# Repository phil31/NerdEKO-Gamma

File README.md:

# Nerd-EKO-Gamma Miner

fork of the NerdOCTAXE-Gamma design (https://github.com/Patsch91/NerdOCTAXE-Gamma), with 12 x BM1370 (14TH/s SHA256)

- 6 layers PCB - Outer / Inner Copper Weight: 2 oz

Design fully tested and validated
consume about 230 Watts on 12V for about 14TH/s (Vcore 1100mV, Icore 180A)
use a 12V 40A PSU

be aware, need some knowledge and tools to build this board !
particulary attention : NEVER power up the board with the Vcore enable without proper heatsink (this will immediatly kill the ASICs !)

## License 
This hardware design is licensed under the TAPR Open Hardware License – Non-Commercial (OHL-NC).  
You are free to use, modify, and distribute for **non-commercial purposes**.  

**Commercial use requires explicit written permission from the copyright holder.**  
See the [LICENSE](LICENSE) file for details.

## Inspired by 
[Bitaxe](https://github.com/skot/bitaxe) 
[NerdAxe](https://github.com/BitMaker-hub)
[NerdOCTAXE](https://github.com/Patsch91/NerdOCTAXE-Gamma) 
[ESP-Miner-NerdQAxePlus](https://github.com/shufps/ESP-Miner-NerdQAxePlus)
[OSMU](https://osmu.wiki/)

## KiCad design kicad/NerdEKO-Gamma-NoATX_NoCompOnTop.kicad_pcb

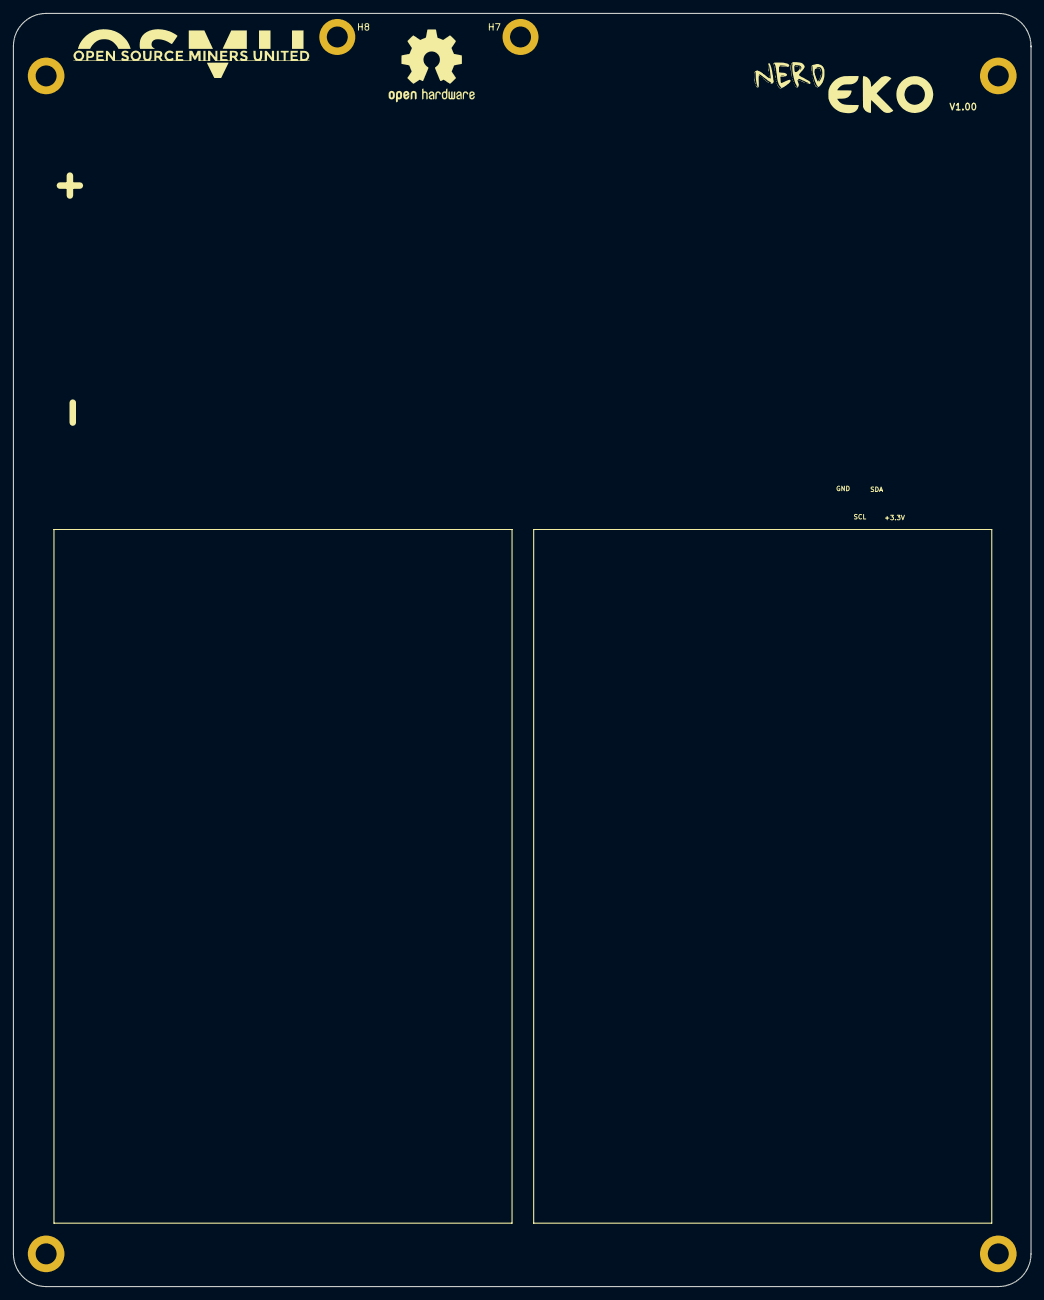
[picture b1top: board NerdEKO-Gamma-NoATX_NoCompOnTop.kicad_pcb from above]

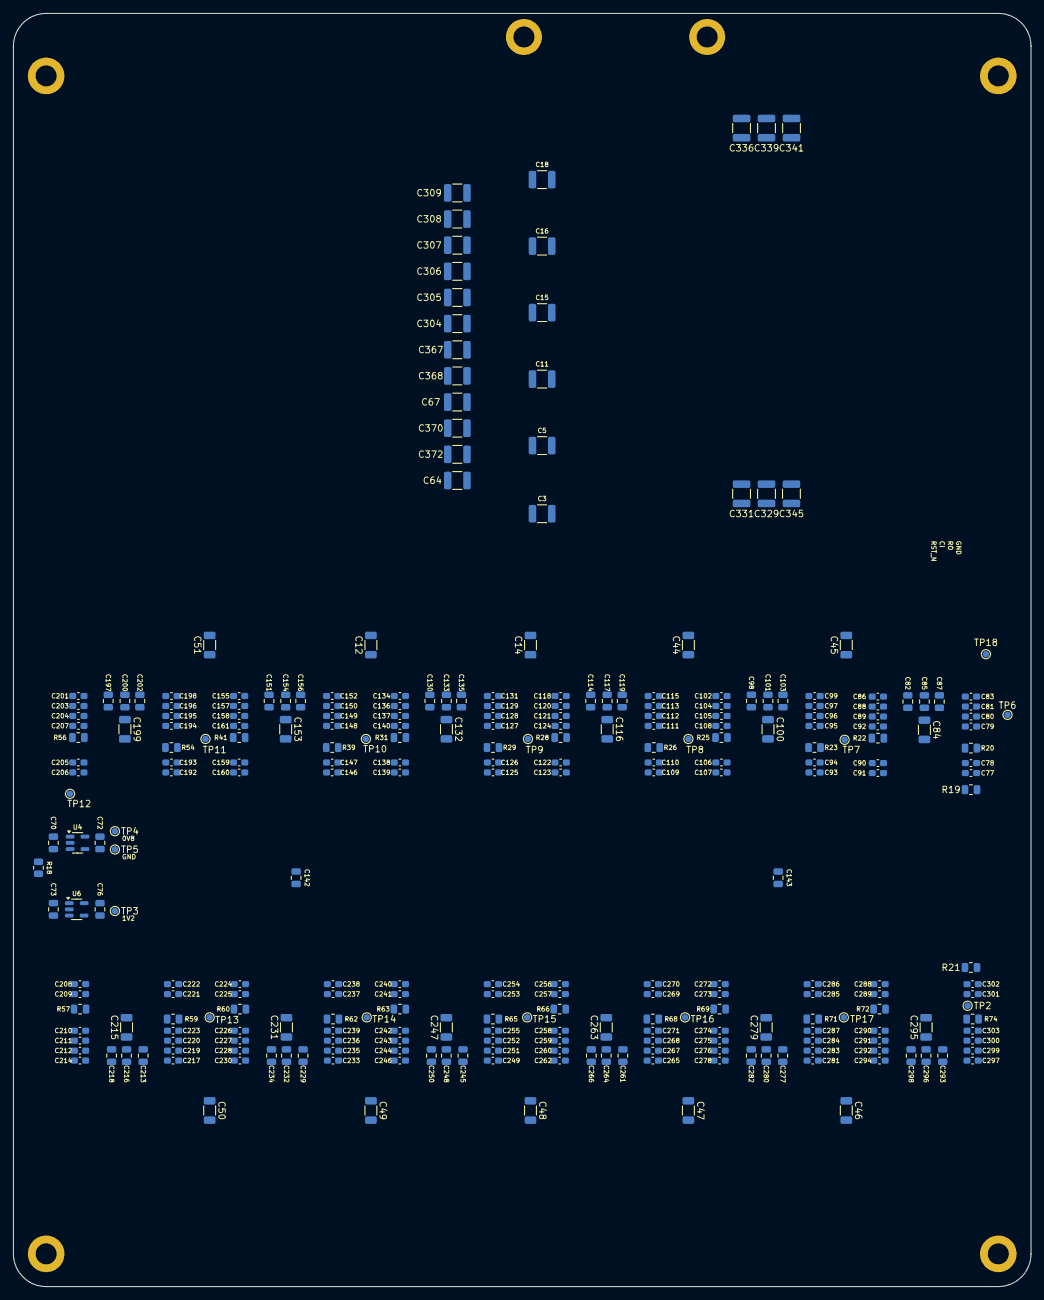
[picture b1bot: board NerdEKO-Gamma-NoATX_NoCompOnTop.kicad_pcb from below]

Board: 6 copper layers, 155.5 x 194.6 mm, 280 parts (278 on the bottom side), 79 nets.

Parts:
C3, C5, C11, C15, C16, C18, C64, C67, C304, C305, C306, C307, C308, C309, C367, C368, C370, C372: 330µF/4V; C_1210_3225Metric
C12, C14, C44, C45, C46, C47, C48, C49, C50, C51, C84, C100, C116, C132, C153, C199, C215, C231, C247, C263, C279, C295: 100µ/6.3V; C_1206_3216Metric
C70, C73, C87, C103, C119, C135, C142, C143, C156, C202, C218, C234, C250, C266, C282, C298: 100nF; C_0805_2012Metric
C72, C76, C85, C101, C117, C133, C154, C200, C216, C232, C248, C264, C280, C296: 1µF/25V; C_0805_2012Metric
C77, C78, C79, C80, C81, C83, C86, C88, C89, C90, C91, C92, C93, C94, C95, C96, C97, C99, C102, C104, C105, C106, C107, C108, C109, C110, C111, C112, C113, C115, C118, C120, C121, C122, C123, C124, C125, C126, C127, C128, C129, C131, C134, C136, C137, C138, C139, C140, C146, C147, C148, C149, C150, C152, C155, C157, C158, C159, C160, C161, C192, C193, C194, C195, C196, C198, C201, C203, C204, C205, C206, C207, C208, C209, C210, C211, C212, C214, C217, C219, C220, C221, C222, C223, C224, C225, C226, C227, C228, C230, C233, C235, C236, C237, C238, C239, C240, C241, C242, C243, C244, C246, C249, C251, C252, C253, C254, C255, C256, C257, C258, C259, C260, C262, C265, C267, C268, C269, C270, C271, C272, C273, C274, C275, C276, C278, C281, C283, C284, C285, C286, C287, C288, C289, C290, C291, C292, C294, C297, C299, C300, C301, C302, C303: 1µF/6.3V; C_0603_1608Metric_Pad1.08x0.95mm_HandSolder
C82, C98, C114, C130, C151, C197, C213, C229, C245, C261, C277, C293: 10µF/25V; C_0805_2012Metric
C329, C331, C336, C339, C341, C345: 22µ/25V; C_1210_3225Metric
H7, H8: MountingHole; MountingHole_3.2mm_M3_ISO14580_Pad
R18, R19, R21: 10K; R_0805_2012Metric
R20, R23, R26, R29, R39, R54, R57, R60, R63, R66, R69, R72: 1K; R_0805_2012Metric
R22, R25, R28, R31, R41, R56, R59, R62, R65, R68, R71, R74: 2K; R_0805_2012Metric
TP2, TP3, TP4, TP5, TP6, TP7, TP8, TP9, TP10, TP11, TP12, TP13, TP14, TP15, TP16, TP17, TP18: TestPoint; TestPoint_Pad_D1.0mm
U4: MCP1824T-0802E; SOT-23-5
U6: MCP1824T-1202E; SOT-23-5

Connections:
+0V8: C72.1, C78.2, C90.2, C94.2, C106.2, C110.2, C122.2, C126.2, C138.2, C147.2, C159.2, C193.2, C205.2, C209.2, C221.2, C225.2, C237.2, C241.2, C253.2, C257.2, C269.2, C273.2, C285.2, C289.2, C301.2, TP4.1, U4.5 (VOUT)
+1V2: C76.1, C77.1, C91.1, C93.1, C107.1, C109.1, C123.1, C125.1, C139.1, C146.1, C160.1, C192.1, C206.1, C208.1, C222.1, C224.1, C238.1, C240.1, C254.1, C256.1, C270.1, C272.1, C286.1, C288.1, C302.1, R21.2, TP3.1, U6.5 (VOUT)
+3V3: C70.1, C73.1, C142.1, C143.1, U4.1 (VIN), U6.1 (VIN)
+12V: C329.1, C331.1, C336.1, C339.1, C341.1, C345.1
/BM1370chain/LDO_EN: R18.1, U4.3 (EN), U6.3 (EN)
GND: C3.2, C5.2, C11.2, C12.2, C14.2, C15.2, C16.2, C18.2, C44.2, C45.2, C46.2, C47.2, C48.2, C49.2, C50.2, C51.2, C64.2, C67.2, C70.2, C72.2, C73.2, C76.2, C77.2, C78.1, C79.1, C82.2, C84.2, C85.2, C87.2, C90.1, C91.2, C92.2, C93.2, C94.1, C95.1, C98.2, C100.2, C101.2, C103.2, C106.1, C107.2, C108.2, C109.2, C110.1, C111.1, C114.2, C116.2, C117.2, C119.2, C122.1, C123.2, C124.2, C125.2, C126.1, C127.1, C130.2, C132.2, C133.2, C135.2, C138.1, C139.2, C140.2, C142.2, C143.2, C146.2, C147.1, C148.1, C151.2, C153.2, C154.2, C156.2, C159.1, C160.2, C161.2, C192.2, C193.1, C194.1, C197.2, C199.2, C200.2, C202.2, C205.1, C206.2, C207.2, C208.2, C209.1, C210.1, C213.2, C215.2, C216.2, C218.2, C221.1, C222.2, C223.2, C224.2, C225.1, C226.1, C229.2, C231.2, C232.2, C234.2, C237.1, C238.2, C239.2, C240.2, C241.1, C242.1, C245.2, C247.2, C248.2, C250.2, C253.1, C254.2, C255.2, C256.2, C257.1, C258.1, C261.2, C263.2, C264.2, C266.2, C269.1, C270.2, C271.2, C272.2, C273.1, C274.1, C277.2, C279.2, C280.2, C282.2, C285.1, C286.2, C287.2, C288.2, C289.1, C290.1, C293.2, C295.2, C296.2, C298.2, C301.1, C302.2, C303.2, C304.2, C305.2, C306.2, C307.2, C308.2, C309.2, C329.2, C331.2, C336.2, C339.2, C341.2, C345.2, C367.2, C368.2, C370.2, C372.2, R18.2, R19.1, R20.2, R22.1, R23.2, R25.1, R26.2, R28.1, R29.2, R31.1, R39.2, R41.1, R54.2, R56.1, R57.2, R59.1, R60.2, R62.1, R63.2, R65.1, R66.2, R68.1, R69.2, R71.1, R72.2, R74.1, TP5.1, U4.2 (GND), U6.2 (GND)
unnamed: C79.2, C80.1
unnamed: C89.2, C92.1
unnamed: C80.2, C81.1
unnamed: C88.2, C89.1
unnamed: C81.2, C83.1
unnamed: C86.2, C88.1
unnamed: C95.2, C96.1
unnamed: C105.2, C108.1
unnamed: C96.2, C97.1
unnamed: C104.2, C105.1
unnamed: C97.2, C99.1
unnamed: C102.2, C104.1
unnamed: C111.2, C112.1
unnamed: C121.2, C124.1
unnamed: C112.2, C113.1
unnamed: C120.2, C121.1
unnamed: C113.2, C115.1
unnamed: C118.2, C120.1
unnamed: C127.2, C128.1
unnamed: C137.2, C140.1
unnamed: C128.2, C129.1
unnamed: C136.2, C137.1
unnamed: C129.2, C131.1
unnamed: C134.2, C136.1
unnamed: C148.2, C149.1
unnamed: C158.2, C161.1
unnamed: C149.2, C150.1
unnamed: C157.2, C158.1
unnamed: C150.2, C152.1
unnamed: C155.2, C157.1
unnamed: C194.2, C195.1
unnamed: C204.2, C207.1
unnamed: C195.2, C196.1
unnamed: C203.2, C204.1
unnamed: C196.2, C198.1
unnamed: C201.2, C203.1
unnamed: C210.2, C211.1
unnamed: C220.2, C223.1
unnamed: C211.2, C212.1
unnamed: C219.2, C220.1
unnamed: C212.2, C214.1
unnamed: C217.2, C219.1
unnamed: C226.2, C227.1
unnamed: C236.2, C239.1
unnamed: C227.2, C228.1
unnamed: C235.2, C236.1
unnamed: C228.2, C230.1
unnamed: C233.2, C235.1
unnamed: C242.2, C243.1
unnamed: C252.2, C255.1
unnamed: C243.2, C244.1
unnamed: C251.2, C252.1
unnamed: C244.2, C246.1
unnamed: C249.2, C251.1
unnamed: C258.2, C259.1
unnamed: C268.2, C271.1
unnamed: C259.2, C260.1
unnamed: C267.2, C268.1
unnamed: C260.2, C262.1
unnamed: C265.2, C267.1
unnamed: C274.2, C275.1
unnamed: C284.2, C287.1
unnamed: C275.2, C276.1
unnamed: C283.2, C284.1
unnamed: C276.2, C278.1
unnamed: C281.2, C283.1
unnamed: C290.2, C291.1
unnamed: C300.2, C303.1
unnamed: C291.2, C292.1
unnamed: C299.2, C300.1
unnamed: C292.2, C294.1
unnamed: C297.2, C299.1
VDD: C3.1, C5.1, C11.1, C12.1, C14.1, C15.1, C16.1, C18.1, C44.1, C45.1, C46.1, C47.1, C48.1, C49.1, C50.1, C51.1, C64.1, C67.1, C82.1, C83.2, C84.1, C85.1, C86.1, C87.1, C98.1, C99.2, C100.1, C101.1, C102.1, C103.1, C114.1, C115.2, C116.1, C117.1, C118.1, C119.1, C130.1, C131.2, C132.1, C133.1, C134.1, C135.1, C151.1, C152.2, C153.1, C154.1, C155.1, C156.1, C197.1, C198.2, C199.1, C200.1, C201.1, C202.1, C213.1, C214.2, C215.1, C216.1, C217.1, C218.1, C229.1, C230.2, C231.1, C232.1, C233.1, C234.1, C245.1, C246.2, C247.1, C248.1, C249.1, C250.1, C261.1, C262.2, C263.1, C264.1, C265.1, C266.1, C277.1, C278.2, C279.1, C280.1, C281.1, C282.1, C293.1, C294.2, C295.1, C296.1, C297.1, C298.1, C304.1, C305.1, C306.1, C307.1, C308.1, C309.1, C367.1, C368.1, C370.1, C372.1

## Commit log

2024-12-08 first release
2025-04-05 final update
    Version 1.0 : working as expected, 14TH/s
2025-04-05 update license
2025-08-07 update firmware link
